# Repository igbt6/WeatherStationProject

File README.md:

WeatherStationProject
=====================

Project of the uszko&amp;kwiecinski weather station

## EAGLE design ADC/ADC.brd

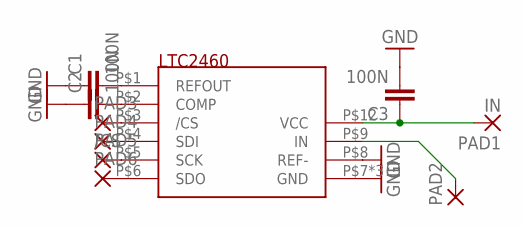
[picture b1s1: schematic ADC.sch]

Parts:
C1, C2, C3: 100N; C0805
PAD1: IN; 2,54/0,8
PAD2, PAD4, PAD5, PAD6: 2,54/0,8
PAD3: /CS; 2,54/0,8
U$1: LTC2460; MSOP8_LT

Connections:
GND: C1.1, C2.1, C3.2, U$1.P$7 (GND), U$1.P$8 (REF-), U$1.P$10 (GND), U$1.P$11 (GND)
unnamed: C1.2, U$1.P$1 (REFOUT)
unnamed: C2.2, U$1.P$2 (COMP)
unnamed: C3.1, PAD1.1, U$1.P$12 (VCC)
unnamed: PAD2.1, U$1.P$9 (IN)
unnamed: PAD3.1, U$1.P$3 (/CS)
unnamed: PAD4.1, U$1.P$4 (SDI)
unnamed: PAD5.1, U$1.P$5 (SCK)
unnamed: PAD6.1, U$1.P$6 (SDO)

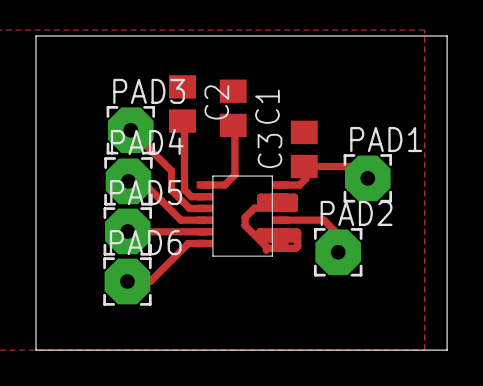
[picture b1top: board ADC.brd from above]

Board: 2 copper layers, 22.8 x 17.4 mm, 10 parts (0 on the bottom side), 9 nets.

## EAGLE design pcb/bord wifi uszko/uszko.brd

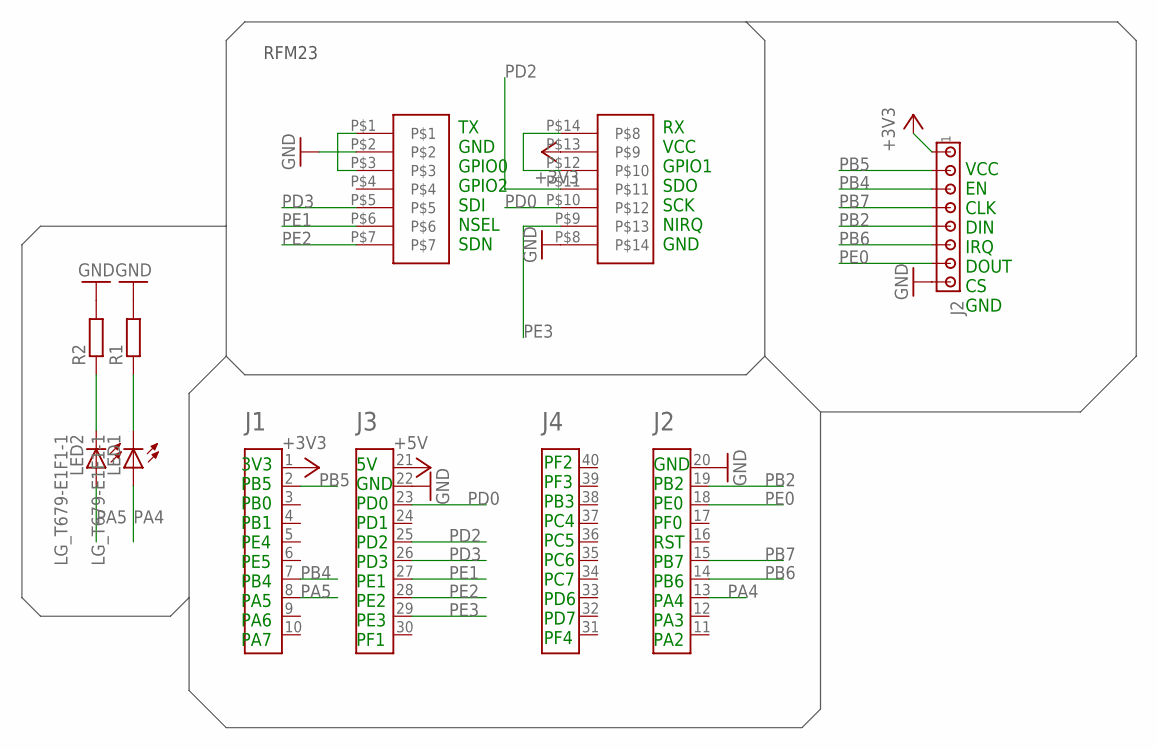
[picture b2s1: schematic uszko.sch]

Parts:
A1: HEADER4X10-BOOSTERPACK; 4X10-BOOSTERPACK
J2: MTA08-100; 10X08MTA
LED1, LED2: LG_T679-E1F1-1; PLCC2
R1, R2: R-EU_R0805; R0805
U$1: 2X7PIN; 2X7PINCON

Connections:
+3V3: A1.1, J2.1, U$1.P$13
+5V: A1.21
GND: A1.20, A1.22, J2.8, R1.2, R2.2, U$1.P$2, U$1.P$8
unnamed: U$1.P$12, U$1.P$14
unnamed: U$1.P$1, U$1.P$3
unnamed: LED1.C, R1.1
unnamed: LED2.C, R2.1
PA4: A1.13, LED1.A
PA5: A1.8, LED2.A
PB2: A1.19, J2.5
PB4: A1.7, J2.3
PB5: A1.2, J2.2
PB6: A1.14, J2.6
PB7: A1.15, J2.4
PD0: A1.23, U$1.P$10
PD2: A1.25, U$1.P$11
PD3: A1.26, U$1.P$5
PE0: A1.18, J2.7
PE1: A1.27, U$1.P$6
PE2: A1.28, U$1.P$7
PE3: A1.29, U$1.P$9

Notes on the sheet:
TX GND GPIO0 GPIO2 SDI NSEL SDN
RX VCC GPIO1 SDO SCK NIRQ GND
3V3 PB5 PB0 PB1 PE4 PE5 PB4 PA5 PA6 PA7
GND PB2 PE0 PF0 RST PB7 PB6 PA4 PA3 PA2
5V GND PD0 PD1 PD2 PD3 PE1 PE2 PE3 PF1
PF2 PF3 PB3 PC4 PC5 PC6 PC7 PD6 PD7 PF4
VCC EN CLK DIN IRQ DOUT CS GND
RFM23

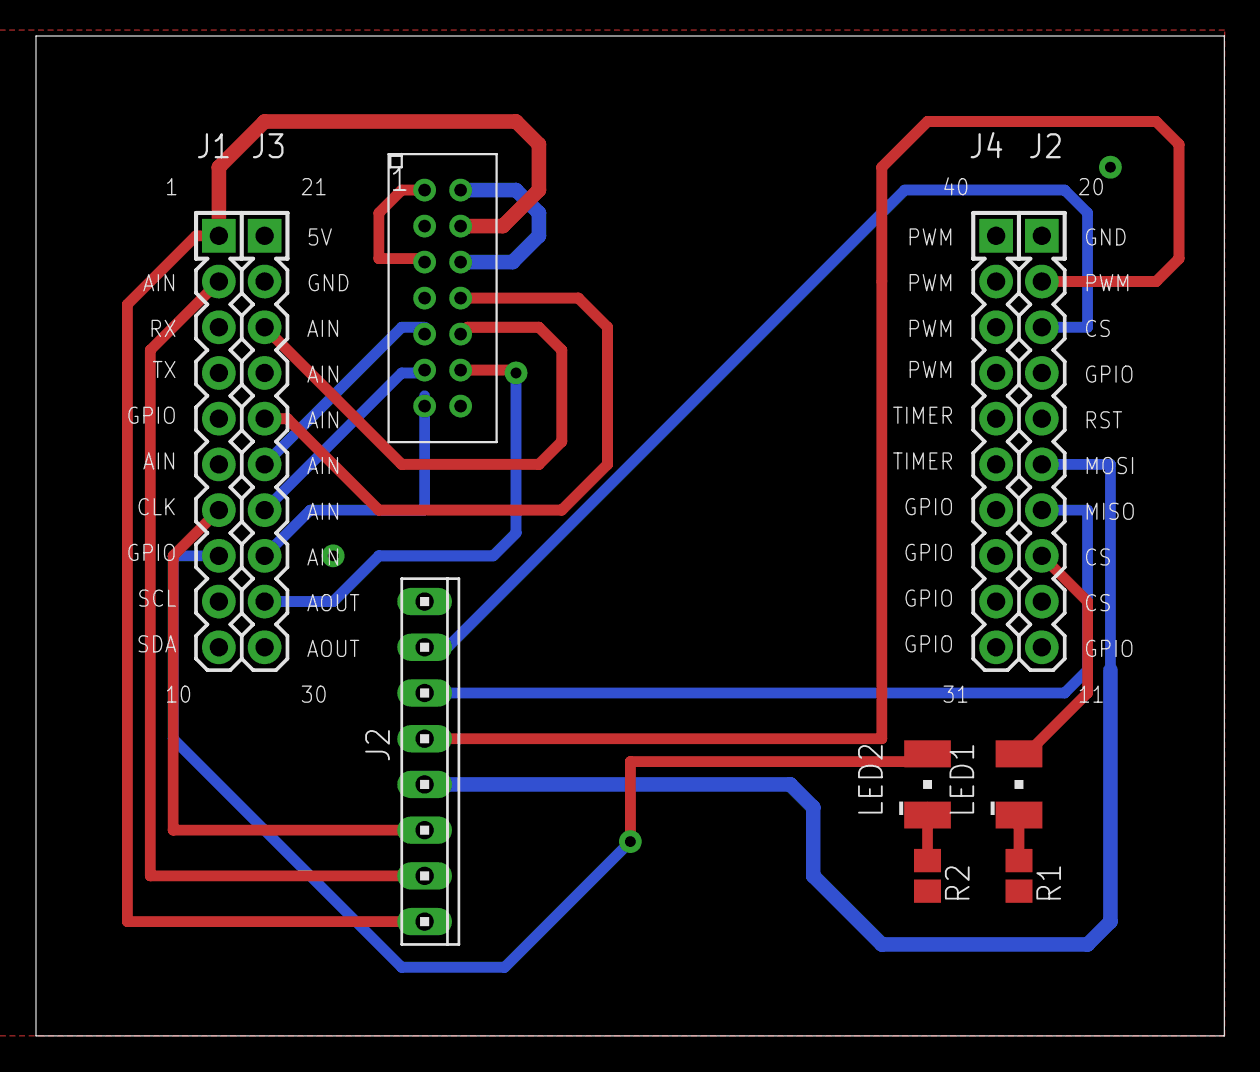
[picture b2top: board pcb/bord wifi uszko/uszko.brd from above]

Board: 2 copper layers, 66.0 x 55.5 mm, 7 parts (0 on the bottom side), 20 nets.

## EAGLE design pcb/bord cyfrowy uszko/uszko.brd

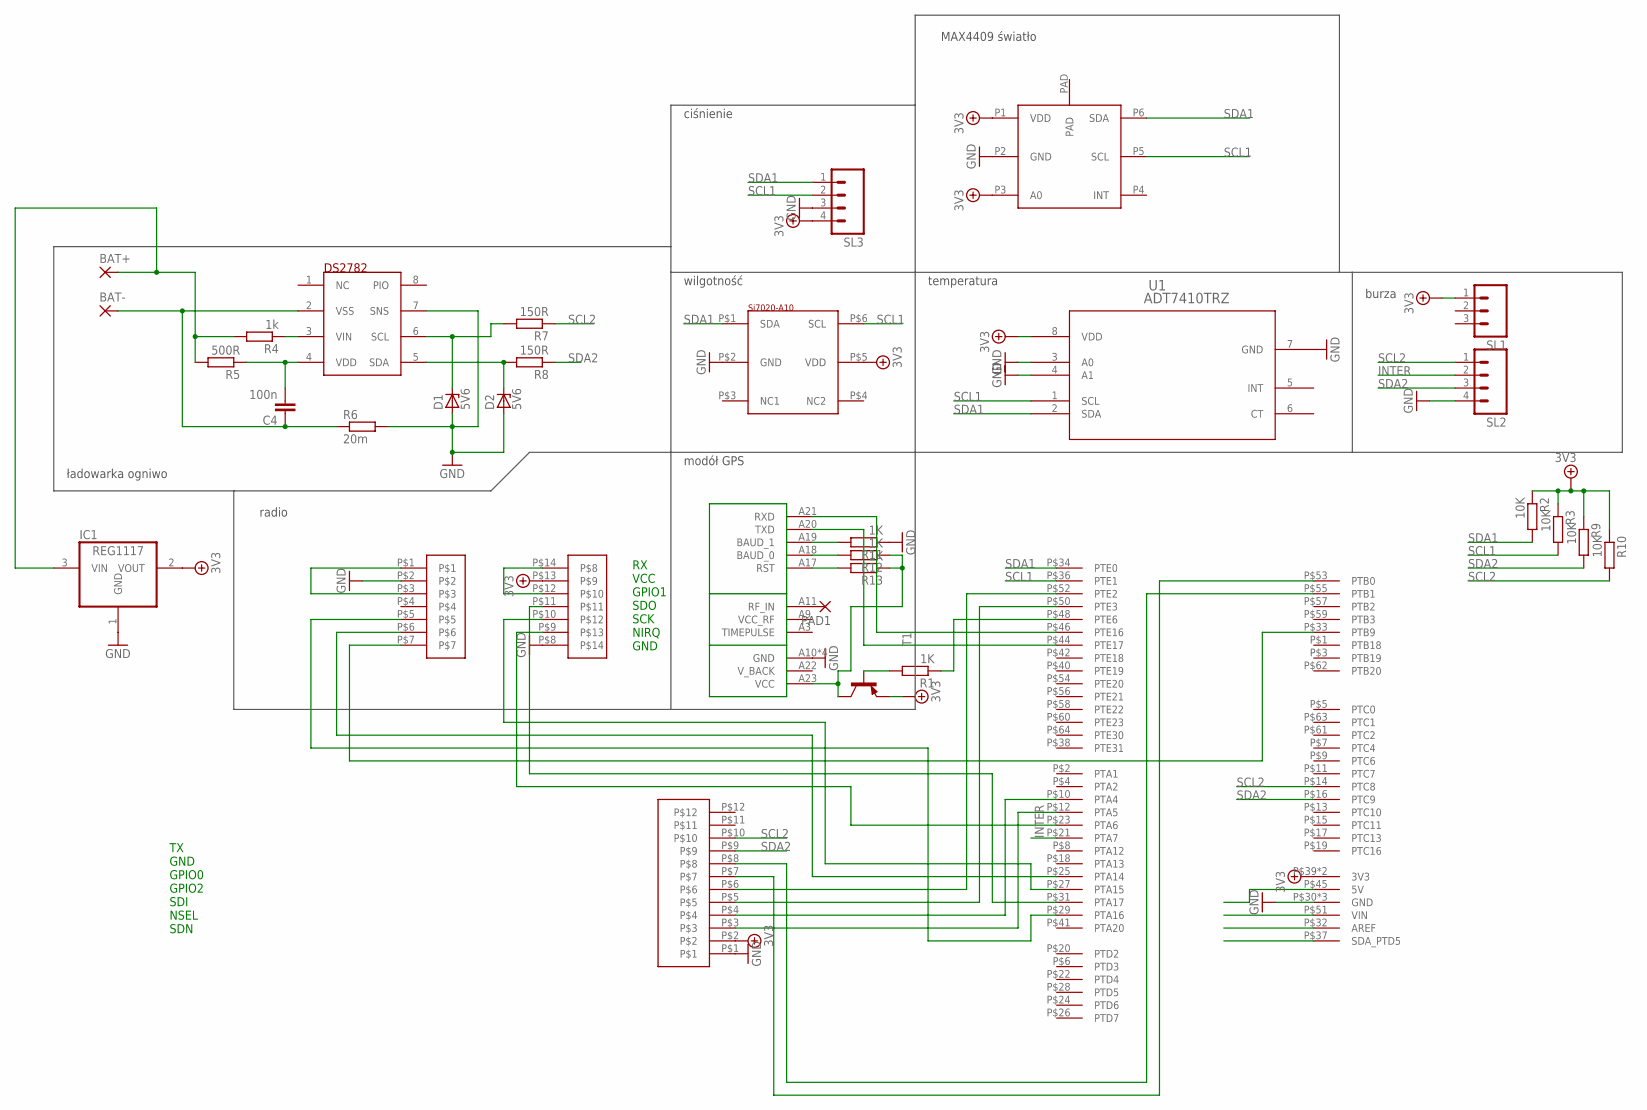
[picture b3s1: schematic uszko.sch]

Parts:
BAT+: 2,54/0,8
BAT-: 2,54/0,8
C4: 100n; C0805
D1, D2: 5V6; SOD80C
IC1: REG1117; SOT223
PAD1: 2,15/1,0
R1, R11, R12, R13: 1K; M0805
R2, R3, R9, R10: 10K; M0805
R4: 1k; M0805
R5: 500R; M0805
R6: 20m; M1206
R7, R8: 150R; M0805
SL1: M03; 03P
SL2, SL3: M04; 04P
T1: -PNP-SOT23-BCE; SOT23-BCE
U1: ADT7410TRZ; R_8
U$1: INTO_CON
U$2: GTS-4E-60
U$3: 2X7PIN; 2X7PINCON
U$4: SI7020-A10; DFN6(3X3MM)
U$5: 12PINCON; 12PIN2MMCON
U$6: MAX44006; 6OTDFN
U$7: DS2782; TSSOP8

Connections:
+5V/1: IC1.2 (VOUT), R2.1, R3.1, R9.1, R10.1, SL1.1, SL3.4, T1.E, U1.8 (VDD), U$1.P$39 (3V3), U$1.P$43 (3V3), U$3.P$13, U$4.P$5 (VDD), U$5.P$2, U$6.P1 (VDD), U$6.P3 (A0)
GND: D1.A, D2.A, IC1.1 (GND), R6.2, R11.1, SL2.4, SL3.3, U1.3 (A0), U1.4 (A1), U1.7 (GND), U$1.P$30 (GND), U$1.P$47 (GND), U$1.P$49 (GND), U$2.A10 (GND), U$2.A12 (GND), U$2.A13 (GND), U$2.A24 (GND), U$3.P$2, U$3.P$8, U$4.P$2 (GND), U$5.P$1, U$6.P2 (GND), U$7.7 (SNS)
INTER: SL2.2, U$1.P$21 (PTA7)
unnamed: U$1.P$46 (PTE16), U$2.A21 (RXD)
unnamed: U$1.P$52 (PTE2), U$5.P$6
unnamed: PAD1.1, U$2.A11 (RF_IN)
unnamed: U$1.P$50 (PTE3), U$5.P$5
unnamed: U$1.P$53 (PTB0), U$5.P$7
unnamed: U$1.P$55 (PTB1), U$5.P$8
unnamed: U$1.P$12 (PTA5), U$5.P$3
unnamed: U$1.P$10 (PTA4), U$5.P$4
unnamed: C4.2, R5.1, U$7.4 (VDD)
unnamed: BAT-.1, C4.1, R6.1, U$7.2 (VSS)
unnamed: R4.1, U$7.3 (VIN)
unnamed: D1.C, R7.2, U$7.6 (SCL)
unnamed: D2.C, R8.2, U$7.5 (SDA)
unnamed: U$3.P$1, U$3.P$3
unnamed: U$3.P$12, U$3.P$14
unnamed: U$1.P$25 (PTA14), U$3.P$6
unnamed: U$1.P$27 (PTA15), U$3.P$10
unnamed: BAT+.1, IC1.3 (VIN), R4.2, R5.2
unnamed: U$1.P$29 (PTA16), U$3.P$5
unnamed: U$1.P$31 (PTA17), U$3.P$11
unnamed: U$1.P$23 (PTA6), U$3.P$9
unnamed: R12.1, R13.1, T1.C, U$2.A23 (VCC)
unnamed: R1.1, U$1.P$48 (PTE6)
unnamed: R1.2, T1.B
unnamed: U$1.P$33 (PTB9), U$3.P$7
unnamed: U$1.P$44 (PTE17), U$2.A20 (TXD)
unnamed: R12.2, U$2.A18 (BAUD_0)
unnamed: R11.2, U$2.A19 (BAUD_1)
unnamed: R13.2, U$2.A17 (RST)
SCL1: R3.2, SL3.2, U1.1 (SCL), U$1.P$36 (PTE1), U$4.P$6 (SCL), U$6.P5 (SCL)
SCL2: R7.1, R10.2, SL2.1, U$1.P$14 (PTC8), U$5.P$10
SDA1: R2.2, SL3.1, U1.2 (SDA), U$1.P$34 (PTE0), U$4.P$1 (SDA), U$6.P6 (SDA)
SDA2: R8.1, R9.2, SL2.3, U$1.P$16 (PTC9), U$5.P$9

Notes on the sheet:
modół GPS
wilgotność
temperatura
MAX4409 światło
ładowarka ogniwo
burza
ciśnienie
radio
TX GND GPIO0 GPIO2 SDI NSEL SDN
RX VCC GPIO1 SDO SCK NIRQ GND

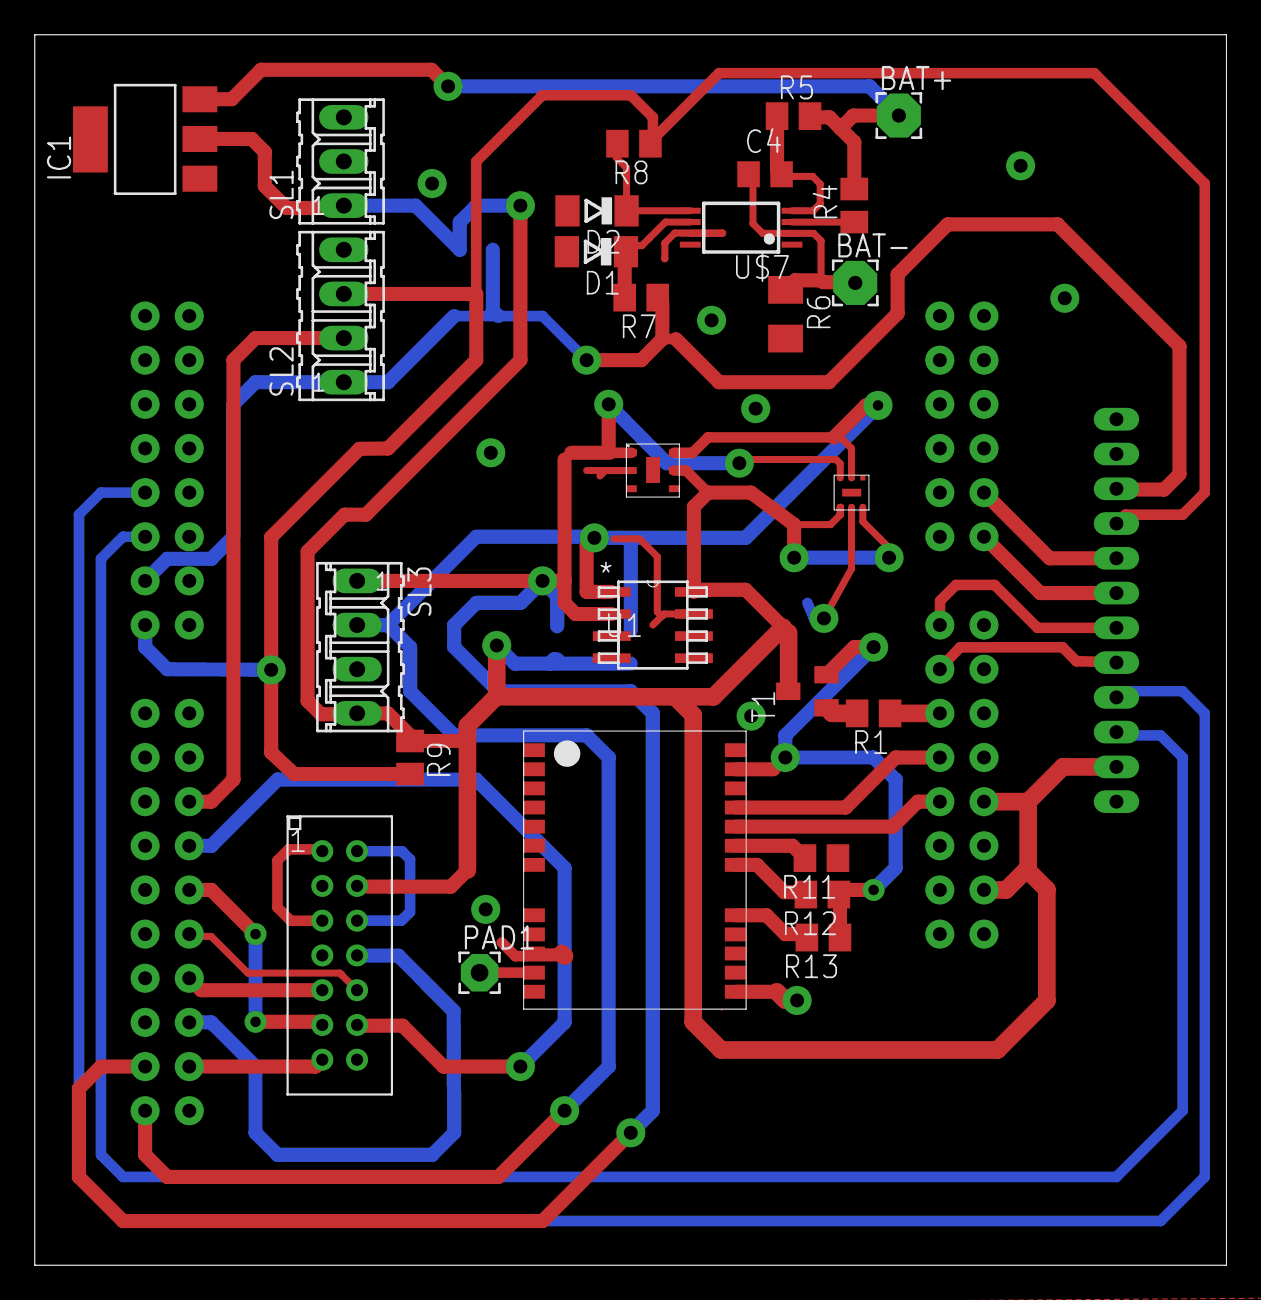
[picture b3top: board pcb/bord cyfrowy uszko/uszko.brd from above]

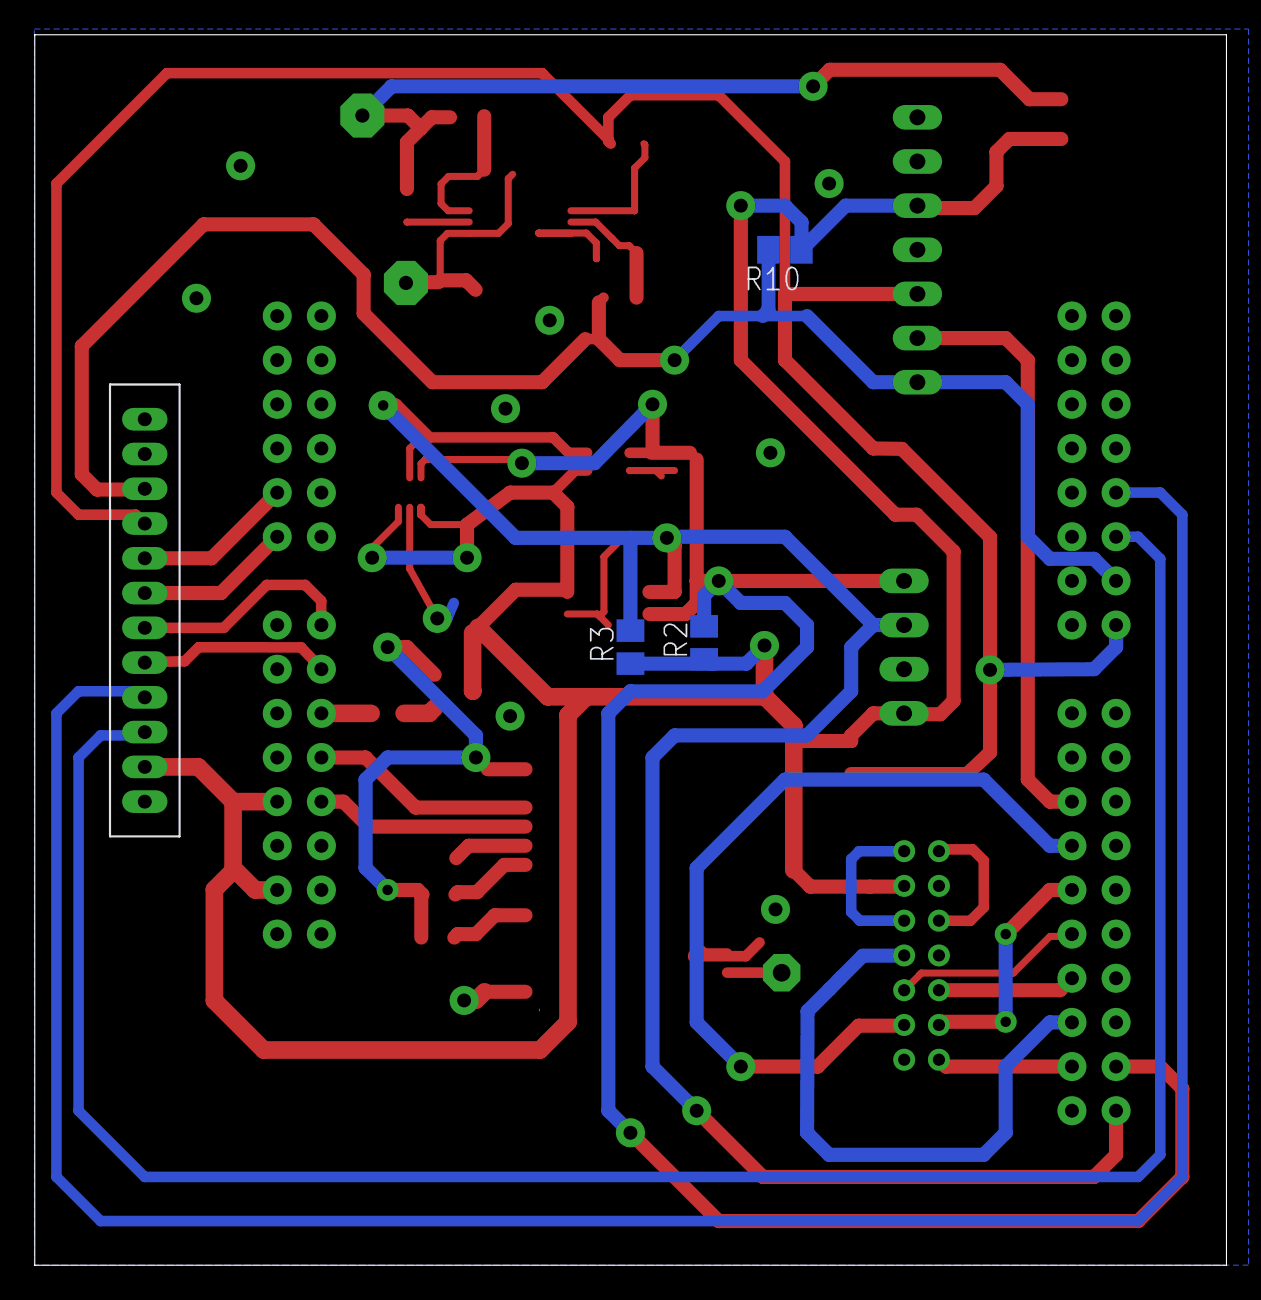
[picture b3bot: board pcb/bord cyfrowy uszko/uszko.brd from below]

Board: 2 copper layers, 68.6 x 70.8 mm, 32 parts (3 on the bottom side), 36 nets.

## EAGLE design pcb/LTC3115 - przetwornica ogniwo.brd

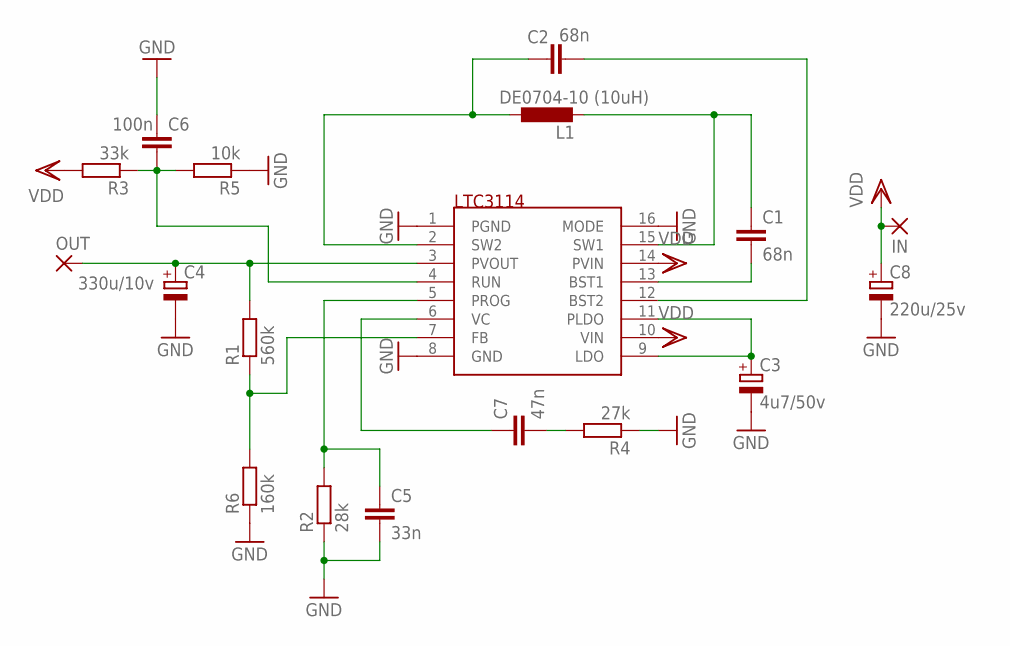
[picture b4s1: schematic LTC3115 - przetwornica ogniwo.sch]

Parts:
C1, C2: 68n; C0805
C3: 4u7/50v; E2,5-6E
C4: 330u/10v; E2,5-6E
C5: 33n; C0805
C6: 100n; C0805
C7: 47n; C0805
C8: 220u/25v; E2,5-6E
IN: 1,6/0,8
L1: DE0704-10 (10uH); L3225M
OUT: 1,6/0,8
R1: 560k; M0805
R2: 28k; M0805
R3: 33k; M0805
R4: 27k; M0805
R5: 10k; M0805
R6: 160k; M0805
U$1: LTC3114; TSSOP16

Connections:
GND: C3.-, C4.-, C5.2, C6.1, C8.-, R2.1, R4.1, R5.1, R6.1, U$1.1 (PGND), U$1.8 (GND), U$1.16 (MODE)
unnamed: C1.2, U$1.13 (BST1)
unnamed: C1.1, L1.2, U$1.15 (SW1)
unnamed: C2.1, U$1.12 (BST2)
unnamed: C2.2, L1.1, U$1.2 (SW2)
unnamed: C3.+, U$1.9 (LDO), U$1.11 (PLDO)
unnamed: R1.1, R6.2, U$1.7 (FB)
unnamed: C4.+, OUT.1, R1.2, U$1.3 (PVOUT)
unnamed: C6.2, R3.1, R5.2, U$1.4 (RUN)
unnamed: C5.1, R2.2, U$1.5 (PROG)
unnamed: C7.2, R4.2
unnamed: C7.1, U$1.6 (VC)
VDD: C8.+, IN.1, R3.2, U$1.10 (VIN), U$1.14 (PVIN)

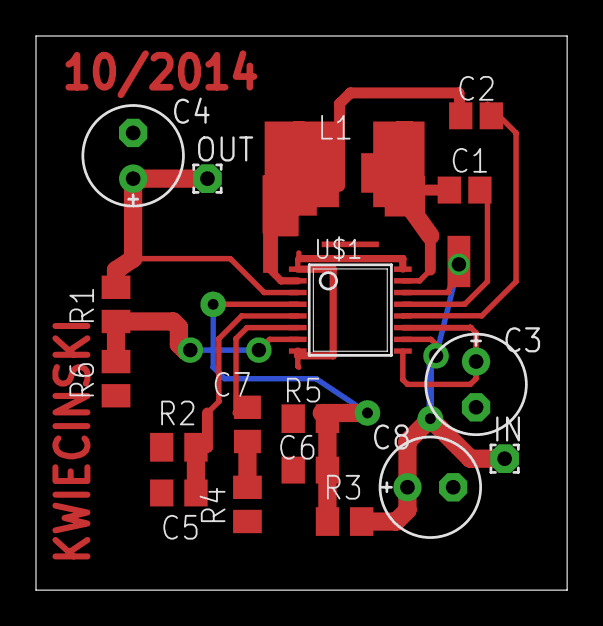
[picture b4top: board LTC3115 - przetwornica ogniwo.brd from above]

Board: 2 copper layers, 29.5 x 30.8 mm, 18 parts (0 on the bottom side), 13 nets.

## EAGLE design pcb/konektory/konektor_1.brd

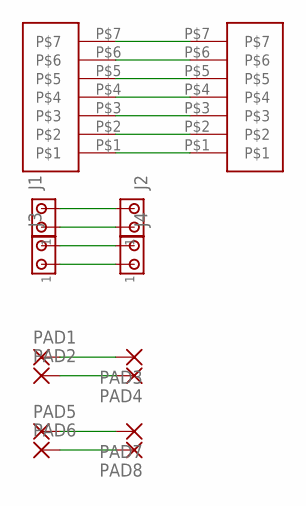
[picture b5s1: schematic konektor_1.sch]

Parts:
J1, J2, J3, J4: MTA02-100; 10X02MTA
PAD1, PAD2, PAD3, PAD4, PAD5, PAD6, PAD7, PAD8: 2,54/0,8
U$1, U$2: 7PIN

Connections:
unnamed: J3.1, J4.1
unnamed: J3.2, J4.2
unnamed: U$1.P$6, U$2.P$6
unnamed: U$1.P$5, U$2.P$5
unnamed: U$1.P$4, U$2.P$4
unnamed: U$1.P$3, U$2.P$3
unnamed: U$1.P$2, U$2.P$2
unnamed: U$1.P$1, U$2.P$1
unnamed: U$1.P$7, U$2.P$7
unnamed: J1.1, J2.1
unnamed: J1.2, J2.2
unnamed: PAD1.1, PAD3.1
unnamed: PAD2.1, PAD4.1
unnamed: PAD5.1, PAD7.1
unnamed: PAD6.1, PAD8.1

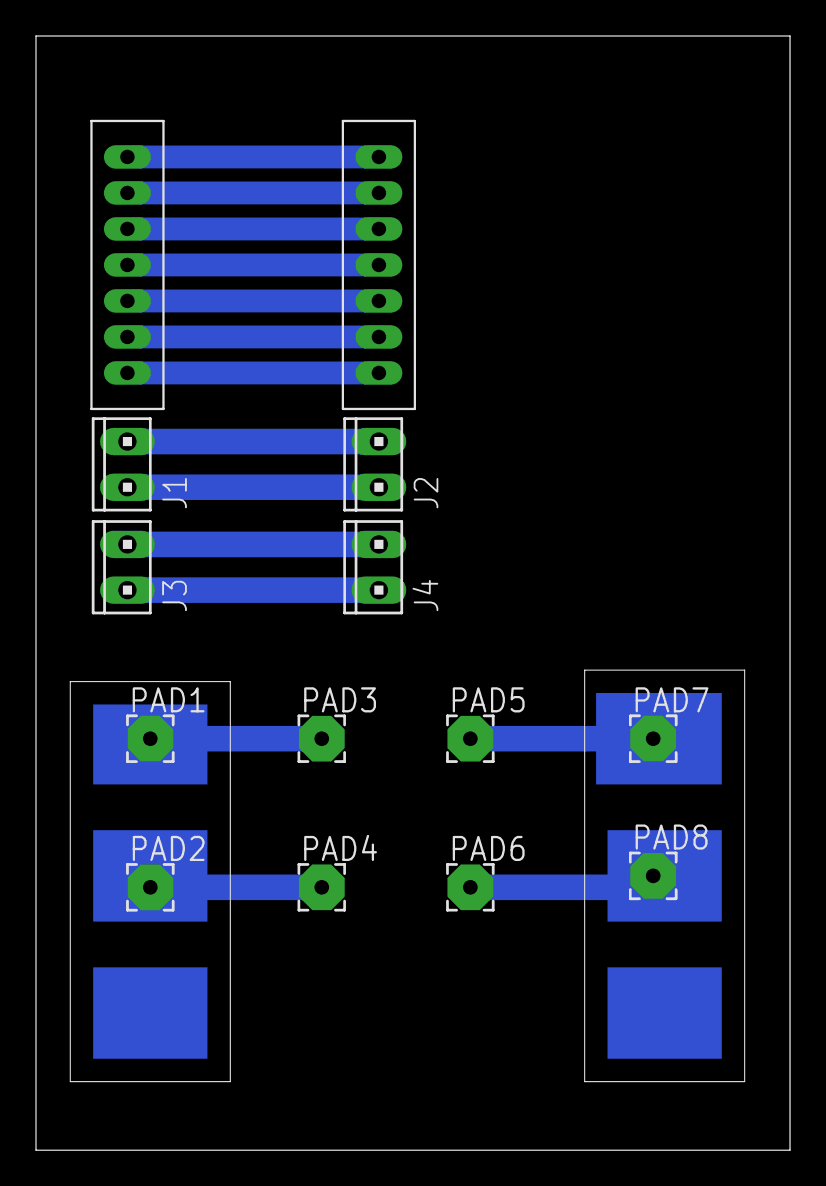
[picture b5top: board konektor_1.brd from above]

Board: 2 copper layers, 41.9 x 61.9 mm, 14 parts (0 on the bottom side), 15 nets.

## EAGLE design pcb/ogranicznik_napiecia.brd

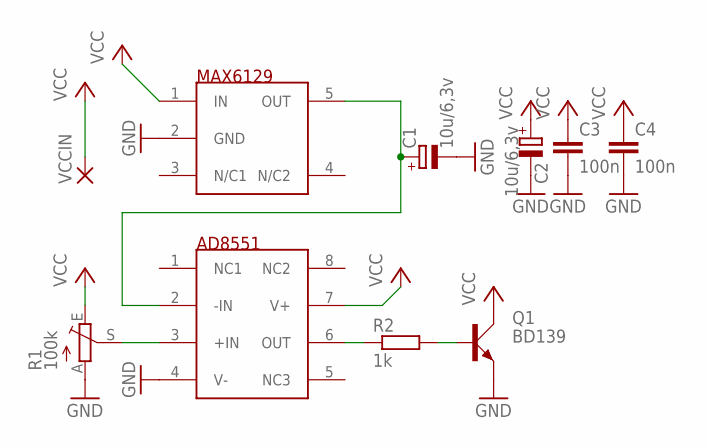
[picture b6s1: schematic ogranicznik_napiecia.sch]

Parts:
C1, C2: 10u/6,3v; SMC_B
C3, C4: 100n; C0805
Q1: BD139; TO126AV
R1: 100k; RJ9W
R2: 1k; M0805
U$1: AD8551; SOIC8
U$2: MAX6129; SOT23-5L
VCCIN: 2,54/0,9

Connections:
GND: C1.-, C2.-, C3.2, C4.2, Q1.E, R1.A, U$1.4 (V-), U$2.2 (GND)
unnamed: Q1.B, R2.2
unnamed: R2.1, U$1.6 (OUT)
unnamed: R1.S, U$1.3 (+IN)
unnamed: C1.+, U$1.2 (-IN), U$2.5 (OUT)
VCC: C2.+, C3.1, C4.1, Q1.C, R1.E, U$1.7 (V+), U$2.1 (IN), VCCIN.1

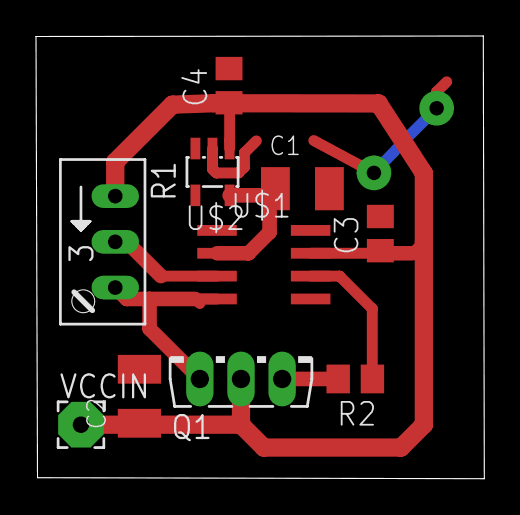
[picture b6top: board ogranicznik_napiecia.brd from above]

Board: 2 copper layers, 24.9 x 24.6 mm, 10 parts (0 on the bottom side), 6 nets.

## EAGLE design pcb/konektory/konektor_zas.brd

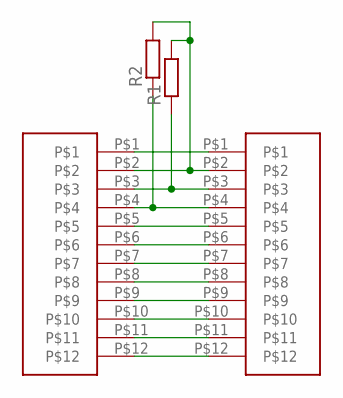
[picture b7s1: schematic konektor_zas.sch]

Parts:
R1, R2: R-EU_R0805; R0805
U$1, U$2: 12PINCON; 12PIN2MMCON

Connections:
unnamed: U$1.P$1, U$2.P$1
unnamed: R1.2, R2.2, U$1.P$2, U$2.P$2
unnamed: R1.1, U$1.P$3, U$2.P$3
unnamed: R2.1, U$1.P$4, U$2.P$4
unnamed: U$1.P$5, U$2.P$5
unnamed: U$1.P$6, U$2.P$6
unnamed: U$1.P$7, U$2.P$7
unnamed: U$1.P$8, U$2.P$8
unnamed: U$1.P$9, U$2.P$9
unnamed: U$1.P$10, U$2.P$10
unnamed: U$1.P$11, U$2.P$11
unnamed: U$1.P$12, U$2.P$12

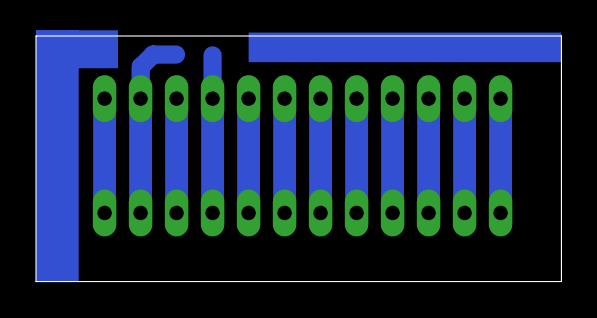
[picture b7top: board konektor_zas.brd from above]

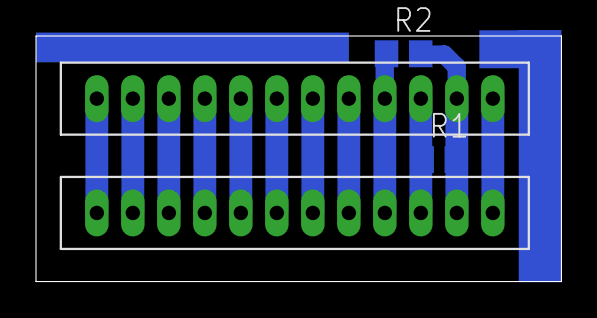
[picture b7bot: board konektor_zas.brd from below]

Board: 2 copper layers, 29.2 x 13.6 mm, 4 parts (2 on the bottom side), 12 nets.

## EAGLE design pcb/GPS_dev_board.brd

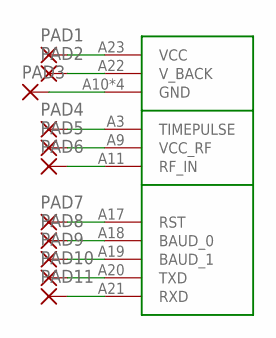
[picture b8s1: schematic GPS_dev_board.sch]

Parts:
PAD1, PAD2, PAD3, PAD4, PAD5, PAD6, PAD7, PAD8, PAD9, PAD10, PAD11: 2,54/0,8
U$1: GTS-4E-60

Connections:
unnamed: PAD1.1, U$1.A23 (VCC)
unnamed: PAD2.1, U$1.A22 (V_BACK)
unnamed: PAD3.1, U$1.A10 (GND), U$1.A12 (GND), U$1.A13 (GND), U$1.A24 (GND)
unnamed: PAD4.1, U$1.A3 (TIMEPULSE)
unnamed: PAD5.1, U$1.A9 (VCC_RF)
unnamed: PAD6.1, U$1.A11 (RF_IN)
unnamed: PAD7.1, U$1.A17 (RST)
unnamed: PAD8.1, U$1.A18 (BAUD_0)
unnamed: PAD9.1, U$1.A19 (BAUD_1)
unnamed: PAD10.1, U$1.A20 (TXD)
unnamed: PAD11.1, U$1.A21 (RXD)

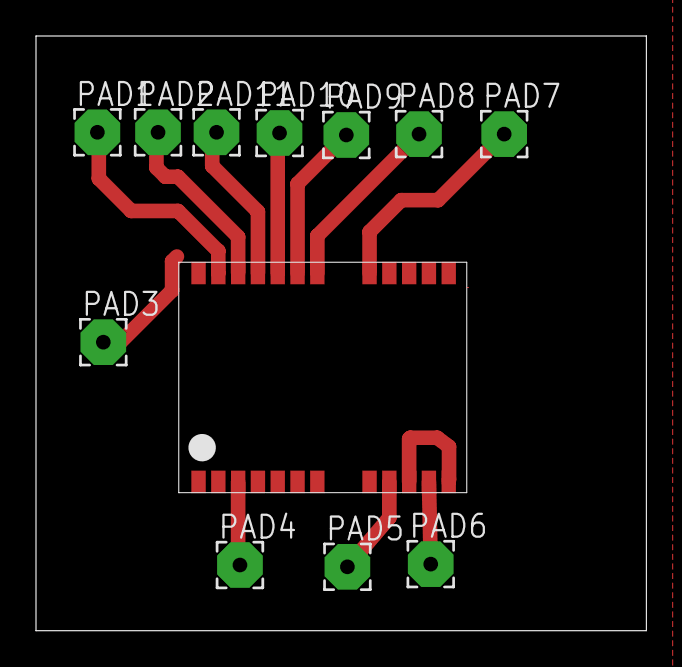
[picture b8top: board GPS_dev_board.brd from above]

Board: 2 copper layers, 33.9 x 33.0 mm, 12 parts (0 on the bottom side), 11 nets.

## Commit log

2014-08-10 unit test doc added
2014-08-12 bibloteka BTM222
2014-08-13 noty+pcb+opis projektu
2014-08-13 some stuff added (datasheets of sensors, 46KLZ docs and others)
2014-08-14 Kinetis reference and programming manuals added
2014-08-19 sample code for frdm46KLZ added, schematics
2014-08-19 folder containing mcu code added
2014-08-20 KDS setup succesfully, sLCD handling added for debug
2014-09-18 PCB przetwornica, aktualizacja kosztorysu
2014-09-18 dokumentacja fotograficzna
2014-10-06 added UART_DEBUGGER
2014-10-06 First setup of MQX Lite RTOS , Debuger task created
2014-10-08 I2C high level api - finished
2014-10-09 library of temp sensor ad7410 finished
2014-10-09 pressure sensor ported
2014-10-10 some changes on i2c library, bmp180 library done finally
2014-10-11 UART improved, waiting for end of transmision and reception of data added
2014-10-12 noty + pcb
2014-10-15 timeout module added- used in i2c
2014-10-16 time dependencies solved , stable version
2014-10-18 bmp180 i2c communication established
2014-10-24 dodanie worda z magisterką gdzie pisze na bierząco, update kosztorysu, nowe bordy
2014-10-26 postępy mgr
2014-10-30 bug :incorrect data from sensors solved ( reason: char tabData instead of uint8_t- shame one me )
2014-11-04 some improvements of main app, test app of the windmill added
2014-11-07 + MAX9611 pinout.txt
2014-11-10 test application MAX9611 added
2014-11-10 bmp180 library finally done
2014-11-11 Max9611 current sensor library added, timing of tasks changed - based on event periodic queues now
2014-11-14 si7020 humidity sensor library 'almost' written ; }
2014-11-15 AS3935 lightning detector - library coding , first tries
2014-11-19 as3935 lightning sensor mbed library written
2014-12-13 fuel gauge tutorial, mgr update
2014-12-13 fuel gauge DS2782 well- done library added
2014-12-14 light sensor algorithm added
2014-12-18 MCU code development under MQX suspended, switched to CMSIS_RTOS and mbed. Libraries of the sensors added
2014-12-18 MCU code development under MQX suspended, switched to CMSIS_RTOS and mbed. Libraries of the sensors added ,quick code cleanup done
2014-12-19 added AS3935 library, some libraries modified to one main cute convention : )
2014-12-20 i2c1 bus works correctly , added needed libraries, code made prettier :)
2014-12-21 AS3935 doesn't work corrctly here, rest of sensors works CORRECTLY- as supposed : )
2014-12-25 postęp w mgr.doc, aktualizacja brd mostek H, GPS dev board
2014-12-27 basic sensors app done
2015-01-01 first version of gps module GPS_GTS-4E-60.lib made. First quite well working demo done :D !
2015-01-02 library for GPS GTS4E60 updated , almost done , works great
2015-01-02 library (ver. 1.0 )for GPS module eventually released, Works great !
2015-01-10 Create MCU_WIFI_MODULE_CODE
    code for WIFI module
2015-01-10 Wifi module - first commit, HTTP client demo app added
2015-01-10 cyclic issuing http GET request added
2015-01-11 android application ver 0.01 added (contains smart configuration of the Wifi module )
2015-01-22 web application, node.js installed, some fun with java script done
2015-01-24 json server first attempts and training done
2015-01-24 post http request added to the demo app
2015-01-28 MAX9611 library updated.
2015-01-29 some big part of tutorials and trainings done :) Simple photo album written !
2015-01-30 arduino source code for MAX9611 added
2015-02-08 mustache templates handled out
2015-02-10 WebApp - training demos removed from the repo
2015-02-12 mysql set up succesfully done
2015-02-14 quick code cleanup, final version implementation has begun !
2015-02-15 mustache template engine applied
2015-02-16 jquerry UI first tests carried out
2015-02-19 bootstrap demo added and set up
2015-02-19 Demo template bootstrap set up - responsive charts added
2015-02-21 fancy home page built. Google maps added
2015-02-21 home page updated , panels' appearance improved
2015-02-21 homepage of the project ver 0.01 released
2015-02-21 Statistics page for all registered stations added
2015-02-22 "About" as a bootstrap modal created
2015-02-22 first version of asynchronous retrieving station data from db implemented , node_modules, and logic of app files moved to app folder (security reasons)
2015-02-23 retrieving data from Db implemented (works well) , mustache template engine added for loading datatables
2015-02-23 rendering data tables of all stations with mustache implemented
2015-02-24 data retrieved from DB correctly and parsed into Tables; content folder created for 'js' and 'css' utils
2015-02-25 station description in DB updated
2015-02-25 select of given column added, retrieving data for a single station - first implementation
2015-02-27 retrieving station by name and id implemented
2015-02-28 reading js script from jqueryy to fire up a new page for single station- done (poor quality : } )
2015-02-28 rewizja bordów
2015-02-28 +mgr
2015-03-01 pinout file for the main board updated
2015-03-02 added pinout .txt file - kwiecinski's test app
2015-03-03 redirect to new page by window.location implemented
2015-03-06 quick cleanup , removed gitignore paths (.txt, .xml and .cpp)
2015-03-06 Test App pinout file created, some stuff moved to Utils folder
2015-03-06 firing up station template from all stations page (first idea )
2015-03-06 RFM23B-433-D.pdf datasheet added (schemat Panie Kwieciński strona 63)
2015-03-07 RFM23b works on the station module side
2015-03-08 Web App design concept totally changed int clear and easy , extensible template pattern (huge work done :) , Pinout updated
2015-03-08 big panel instead of metis-menu to store and handle all options
2015-03-09 some sample charts added to be used in app
2015-03-10 RFM23B library added for WIFi side. init of the module correctly carried out
2015-03-15 rfm23d server side handled - problems with communication still remain
2015-03-16 working transmision between Client-server RFM23
2015-03-16 bord dla uszka, prezentacja
2015-03-17 Pinout update concerning RFM23
2015-03-19 /RFM23d reliable transmission succesfully setup
2015-03-20 handling RFM23 module built in our RTOS threads
2015-03-25 pcb uszko
2015-03-29 bord uszko, piout update
2015-04-01 gps shutdown pin added
2015-04-08 mgr, pcb uszko
2015-04-12 permanent connection between WIFI module and station created ( wifi modules periodically asks station and then meteo data are being sent back to the module)
2015-04-13 json serializing data implemented
2015-04-13 timer mechanism for cyclic checking state of connection with station implemented
2015-04-18 checking connection with station in timer interrupt handler
2015-04-20 pinout updated for wifi module
2015-04-23 made CC3000 cooperate with RFM23B almost done on WIFI module
2015-04-23 json packages send to Wifi module
2015-04-24 receiving correct json data packets done
2015-04-25 + ADC
2015-04-26 web app updated - station info label added
2015-05-10 added test mcu app with LTC2460 ADC converter for kwiecinski
2015-05-12 update pcb
2015-05-14 first ver of mgr doc added
2015-05-14 my diploma thesis zipped and hashed
2015-05-15 creating descriptions for each station module began
2015-05-16 RFM23-D and ADT7410 descriptions added
2015-05-20 more desc of sensors added
2015-05-20 descriptions of all sensors for station module finished
2015-05-21 Msc Presntation and photos added, Wifi CC3000 module - description started
2015-05-23 CC3000 description added
2015-05-31 coding part description begins
2015-06-03 sotware of CC3000 - description finished
2015-06-03 i2c checker short description added
2015-06-05 Node.js introduction added
2015-06-06 Server description done
2015-06-09 server side description finished
2015-06-09 Mobile Apps desc done
2015-06-09 future plans added
2015-06-10 first version of my MSc thesis prepared
2015-06-12 mcu code works well after porting to new board
2015-06-29 improved mcu code , works quite well, some bugs fixed, gps handler modified
2015-06-29 final version of mgr doc prepared
2015-08-04 aJson lib added, unused modules updated
2015-08-05 data parser class implemnt
2015-08-06 incoming data parser - first implementation
2015-08-07 data parser for hum works pretty well
2015-08-12 data parser demo version finished
2015-08-14 sarialization object implementation
2015-08-15 serializer improved
2015-08-19 parser for meteo data ready to be launched
2015-09-16 wifi module code ported to nucleo - first commit
2015-09-17 RFM23 forced to work on nucleo, data parsers modified as well
2015-09-21 working RFM23d added
